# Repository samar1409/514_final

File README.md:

# Portable Air Quality Monitoring System

## Overview
This project consists of two devices: a portable air quality sensing device and a desktop display device. The sensing device collects air quality data, including CO2 and PM2.5 levels, and wirelessly transmits the data to the display device. The display device provides a clear, real-time visualization using a stepper motor-driven needle, LEDs, and a tactile button.

## Sketch of the System

---

## Sensing Device

### Description
The sensing device is a compact handheld unit equipped with the following components:

- **Sensors:**
  - **CO2 Sensor:** [SCD30](https://sensirion.com/products/catalog/SCD30/)
  - **PM2.5 Sensor:** [PMS5003](https://learn.adafruit.com/pm25-air-quality-sensor)
- **Microcontroller:** ESP32 (for wireless communication via Wi-Fi/Bluetooth)
- **Battery:** Rechargeable LiPo battery (3.7V, 2000mAh)
- **Enclosure:** Lightweight and durable plastic case

### How It Works
The CO2 sensor measures the concentration of carbon dioxide in the air, while the PM2.5 sensor measures fine particulate matter. The ESP32 processes the sensor data and transmits it wirelessly to the display device via Wi-Fi. The device is powered by a rechargeable LiPo battery.

---

## Display Device

### Description
The display device is a compact desktop unit featuring:

- **Output Devices:**
  - Stepper Motor with Needle Gauge: [28BYJ-48 + ULN2003 Driver](https://lastminuteengineers.com/28byj48-stepper-motor-arduino-tutorial/)
  - RGB LED Indicators
- **Input Device:**
  - Tactile Push Button
- **Microcontroller:** Arduino Nano
- **Battery:** Rechargeable LiPo battery (3.7V, 1200mAh)
- **Enclosure:** Compact plastic housing

### How It Works
The Arduino Nano receives air quality data wirelessly from the sensing device. It drives the stepper motor to move the needle on the gauge, indicating air quality levels. RGB LEDs provide visual alerts for specific pollutant thresholds, and the tactile button resets threshold settings.

---

## System Architecture

### How the Devices Communicate
The ESP32 on the sensing device collects sensor data and transmits it to the Arduino Nano on the display device via Wi-Fi using the MQTT protocol for lightweight and efficient communication.

### Diagram

#### Architecture

#### Workflow
1. The CO2 and PM2.5 sensors collect air quality data.
2. The ESP32 processes the data and transmits it via Wi-Fi.
3. The Arduino Nano receives the data and drives the stepper motor, RGB LEDs, and tactile button on the display device.

---

## Datasheets

The datasheets for the following components are included in the `datasheets/` directory:

- [SCD30 (CO2 Sensor)](https://www.sensirion.com/en/environmental-sensors/carbon-dioxide-sensors/carbon-dioxide-sensor-scd30/)
- [PMS5003 (PM2.5 Sensor)](https://learn.adafruit.com/pm25-air-quality-sensor)
- [ESP32 Microcontroller](https://www.espressif.com/en/products/socs/esp32)
- [Arduino Nano](https://store.arduino.cc/products/arduino-nano)
- [28BYJ-48 Stepper Motor + ULN2003 Driver](https://lastminuteengineers.com/28byj48-stepper-motor-arduino-tutorial/)

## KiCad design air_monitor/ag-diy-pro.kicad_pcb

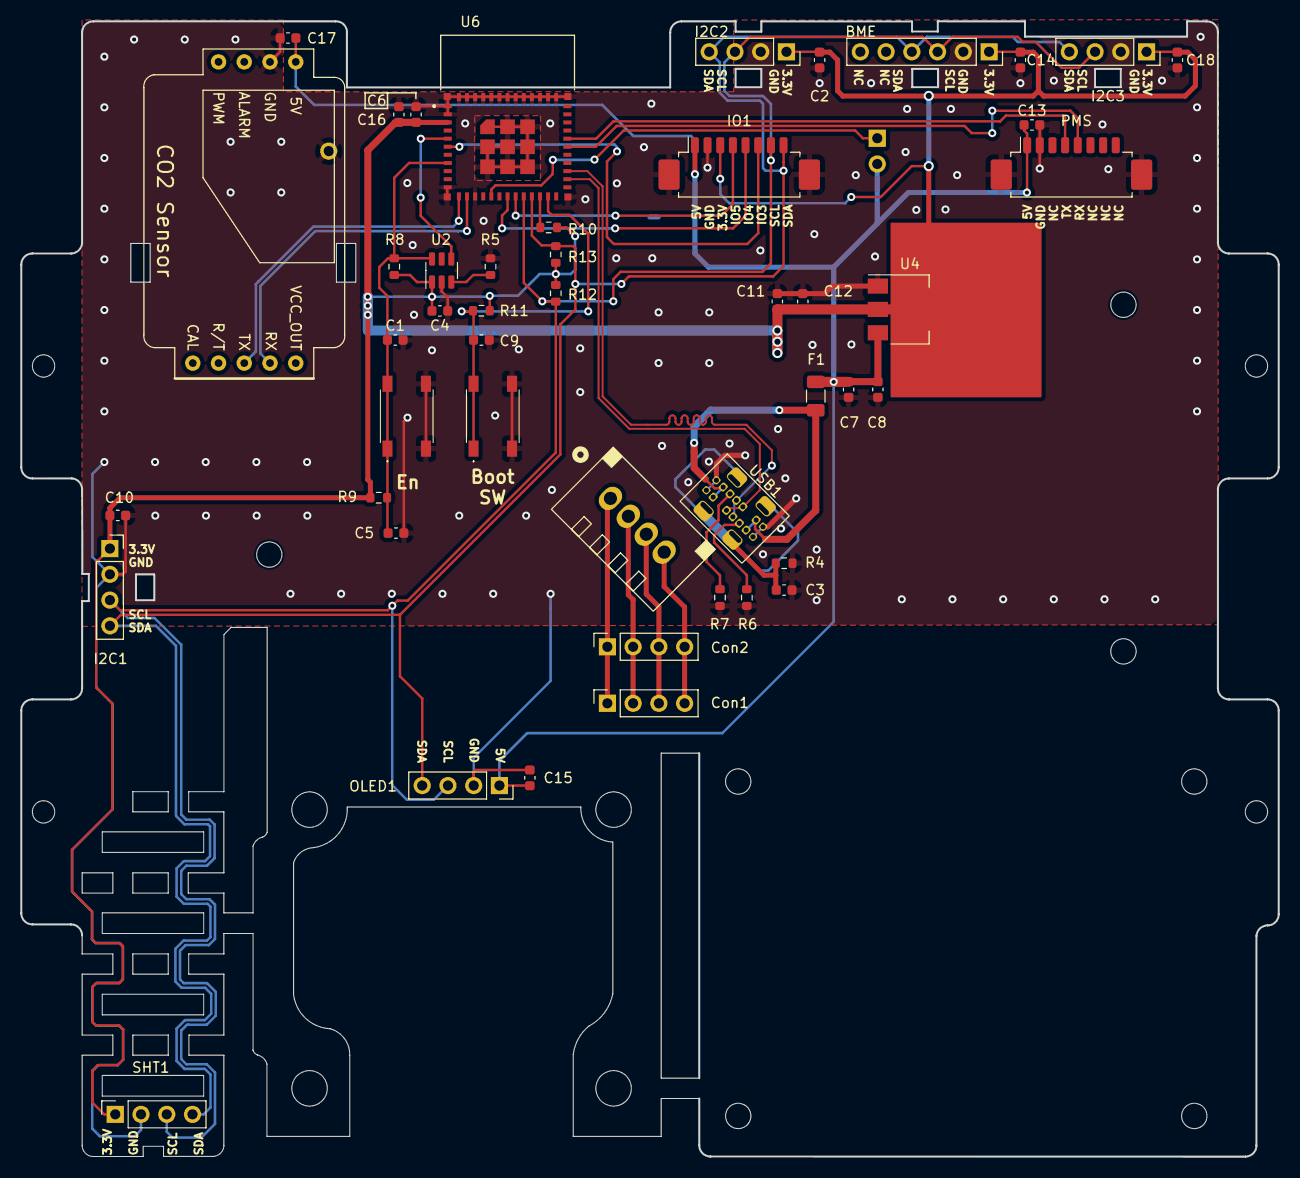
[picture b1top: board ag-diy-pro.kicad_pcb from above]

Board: 2 copper layers, 124.1 x 112.0 mm, 48 parts (1 on the bottom side), 28 nets.

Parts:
Boot1: SW_Push_Dual; PTS525SM08SMTR2LFS
C1, C9: 0.01uf; C_0603_1608Metric
C2, C3, C4, C6, C8, C10, C12, C13, C14, C15, C17, C18: 0.1uf; C_0603_1608Metric
C5: 1uf; C_0603_1608Metric
C7: 10uf / 25V; C_0603_1608Metric
C11, C16: 22uf / 10V; C_0603_1608Metric
Con1, Con2: Conn_01x04; PinSocket_1x04_P2.54mm_Vertical
F1: 1A 16V; Fuse_1206_3216Metric
I2C1, I2C2, I2C3: Conn_01x04; PinSocket_1x04_P2.54mm_Vertical
IO1: Conn_01x08_MountingPin; Molex_PicoBlade_53261-0871_1x08-1MP_P1.25mm_Horizontal
OLED1: Conn_01x04; PinSocket_1x04_P2.54mm_Vertical
PM2: Conn_01x08_MountingPin; Molex_PicoBlade_53261-0871_1x08-1MP_P1.25mm_Horizontal
R4, R8: 100K; R_0603_1608Metric
R5: 51K; R_0603_1608Metric
R6, R7: 5.1K; R_0603_1608Metric
R9, R10, R11, R12, R13: 10K; R_0603_1608Metric
RS1: Screw_Terminal_01x04; Modbus_2.5_CONN
Reset1: SW_Push_Dual; PTS525SM08SMTR2LFS
S*1: BME; PinSocket_1x06_P2.54mm_Vertical
S*2: Co2-S8
SHT1: Conn_01x04; PinSocket_1x04_P2.54mm_Vertical
U2: TPL5010; SOT-23-6
U4: LM1117-3.3; SOT-223-3_TabPin2
U5: 11Dots_LedBar
U6: ESP32-C3-MINI-1-N4; XCVR_ESP32-C3-MINI-1-N4
USB1: 918-418K2022Y40000

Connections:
+3.3V: C2.1, C4.2, C6.2, C10.1, C11.1, C12.1, C14.1, C16.1, C18.1, I2C1.1, I2C2.1, I2C3.1, IO1.3, R8.1, R9.1, R10.2, R11.1, R12.1, R13.1, S*1.1 (3.3V), SHT1.1, U2.1 (VDD), U4.2 (VO), U6.3 (+3.3V)
+5V: C7.1, C8.1, C13.1, C15.1, C17.1, F1.1, IO1.1, OLED1.1, PM2.1, S*2.1 (5V), U4.3 (VI), U5.2 (VDD)
/BOOT: Boot1.1, Boot1.2, C9.1, R11.2, U6.23 (IO9)
/EN: C1.1, C5.1, R8.2, R9.2, Reset1.1, Reset1.2, U2.6 (~RST), U6.8 (EN)
/IO3: IO1.6, U6.6 (IO3)
/IO4: IO1.5, U6.18 (IO4)
/IO5: IO1.4, U6.19 (IO5)
/LED: U5.1 (Din), U6.16 (IO10)
/RX_1_PMS: PM2.5, U6.30 (RXD0)
/RX_2_PMS: S*2.7 (TX), U6.12 (IO0)
/SCL: I2C1.3, I2C2.3, I2C3.3, IO1.7, OLED1.3, R12.2, S*1.3 (SCL), SHT1.3, U6.20 (IO6)
/SDA: I2C1.4, I2C2.4, I2C3.4, IO1.8, OLED1.4, R13.2, S*1.4 (SDA), SHT1.4, U6.21 (IO7)
/TX_1_PMS: PM2.4, U6.31 (TXD0)
/TX_2_PMS: S*2.6 (RX), U6.13 (IO1)
/USB_D+: U6.27 (IO19), USB1.A6 (D+), USB1.B6 (D+)
/USB_D-: U6.26 (IO18), USB1.A7 (D-), USB1.B7 (D-)
/WD_RST: U2.4 (DONE), U6.5 (IO2)
GND: Boot1.3, Boot1.4, C1.2, C2.2, C3.2, C4.1, C5.2, C6.1, C7.2, C8.2, C9.2, C10.2, C11.2, C12.2, C13.2, C14.2, C15.2, C16.2, C17.2, C18.2, I2C1.2, I2C2.2, I2C3.2, IO1.2, IO1.MP (MountPin), OLED1.2, PM2.2, PM2.MP (MountPin), R4.2, R5.2, R6.2, R7.2, Reset1.3, Reset1.4, S*1.2 (GND), S*2.2 (Gnd), SHT1.2, U2.2 (GND), U4.1 (GND), U5.3 (VSS), U6.1 (GND), U6.2 (GND), U6.11 (GND), U6.14 (GND), U6.36 (GND), U6.37 (GND), U6.38 (GND), U6.39 (GND), U6.40 (GND), U6.41 (GND), U6.42 (GND), U6.43 (GND), U6.44 (GND), U6.45 (GND), U6.46 (GND), U6.47 (GND), U6.48 (GND), U6.49_1 (GND), U6.49_2 (GND), U6.49_3 (GND), U6.49_4 (GND), U6.49_5 (GND), U6.49_6 (GND), U6.49_7 (GND), U6.49_8 (GND), U6.49_9 (GND), U6.50 (GND), U6.51 (GND), U6.52 (GND), U6.53 (GND), USB1.A1 (GND), USB1.A12 (GND), USB1.B1 (GND), USB1.B12 (GND)
unnamed: Con1.1, Con2.1, RS1.1
unnamed: Con1.2, Con2.2, RS1.2
unnamed: Con1.3, Con2.3, RS1.3
unnamed: Con1.4, Con2.4, RS1.4
unnamed: F1.2, USB1.A4 (VBUS), USB1.A9 (VBUS), USB1.B4 (VBUS), USB1.B9 (VBUS)
unnamed: R5.1, U2.3 (DELAY/M_RST)
unnamed: R10.1, U6.22 (IO8)
unnamed: R7.1, USB1.A5 (CC1)
unnamed: R6.1, USB1.B5 (CC2)
unnamed: C3.1, R4.1, USB1.S1 (SHIELD)

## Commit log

2025-01-21 images commit
2025-01-21 add sketch.png to readme
2025-01-21 sensiron link commit
2025-01-21 readme final
2025-01-22 datasheets commit
2025-01-29 Create fdkfsa
2025-01-29 sch v4
2025-01-29 sch v5
2025-02-06 pcb design final
2025-02-14 spreadsheet power
2025-03-12 ML update
